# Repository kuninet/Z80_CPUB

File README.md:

# Z80マイコンCPUボード (KZ80-CPUB)

- SBC8080バスにつながるZ80 CPUボード KZ80-CPUB のデータ類です。
  - CPUボード+[SBC8080 SUBルーズキット](https://vintagechips.wordpress.com/2018/06/23/sbc8080-subルーズキット/)などとのセットでコンピューターとして動作します。(単独では動きません)

- 回路図、部品等の詳しい説明を記載したwikiページは以下になります。
  - https://github.com/kuninet/Z80_CPUB/wiki

## ファイル/ディレクトリ

ファイル/ディレクトリの構成は以下のとおりです

|ファイル/ディレクトリ|概要|
|:--|:--|
|KiCAD/PCB/|基板製造用ガーバーファイル等|
|KiCAD/Z80-CPUB.ods|部品一覧表|
|img/Z80-CPUB.pdf|回路図 PDF版|
|KiCAD/Z80-CPUB*.*|KiCADファイル|

## 注意点

- REV1基板はSBC8080ルーズキットと完全互換ではありません。
  - DMAは行なえません。(#BUSREQ/#BUSACKに対応していない)
  - DMAに伴う#IOR/Wや#MEMR/Wのハイインピーダンス対応を実施していません。

## ライセンス

- 本リポジトリのデータは MIT License のもとで公開します。[LICENSE.txt](LICENSE.txt)を参照して下さい。

## 参照

[電脳伝説:SBC8080ルーズキット](https://vintagechips.wordpress.com/2018/06/24/sbc8080-cpu%E3%83%AB%E3%83%BC%E3%82%BA%E3%82%AD%E3%83%83%E3%83%88/)

[SBC8080 SUBボードへつなぐZ80 CPUボードの作成](https://kuninet.org/2018/08/01/sbc8080-subボードへつなぐz80-cpuボードの作成/)

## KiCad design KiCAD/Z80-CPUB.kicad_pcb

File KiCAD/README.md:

# Z80 CPUボード

## 概要

- SBC8080ルーズキットのバス(SBC8080バスと呼称)につながるZ80 CPUボードのKiCADデータです。

## ファイル/ディレクトリ

ファイル/ディレクトリの構成は以下のとおりです

|ファイル/ディレクトリ|概要|
|:--|:--|
|PCB/|基板製造用ガーバーファイル等|
|Z80-CPUB.ods|部品一覧表|
|Z80-CPUB.pdf|回路図 PDF版|
|Z80-CPUB*.*|KiCADファイル|

## 注意点

- REV1基板は、SBC8080ルーズキットと完全互換ではありません。
  - DMAは行なえません。(#BUSREQ/#BUSACKに対応していない)
  - DMAに伴う#IOR/Wや#MEMR/Wのハイインピーダンス対応を実施していません。

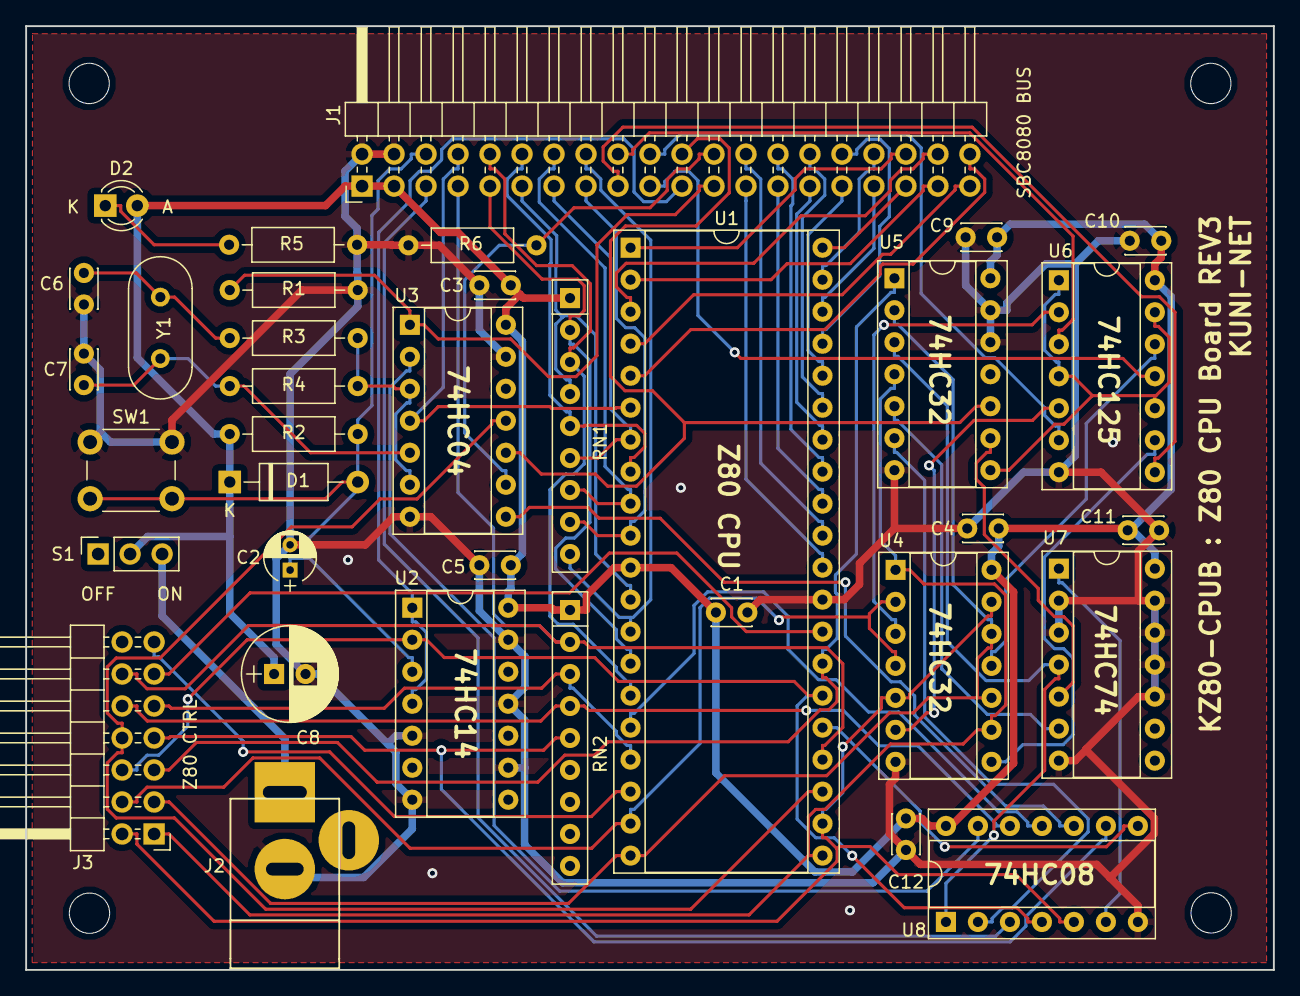
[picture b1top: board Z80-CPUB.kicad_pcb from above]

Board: 2 copper layers, 99.1 x 74.9 mm, 40 parts (0 on the bottom side), 69 nets.

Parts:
C1, C3, C4, C5, C9, C10, C11, C12: 0.1u; C_Disc_D3.0mm_W2.0mm_P2.50mm
C2: 47u; CP_Radial_D4.0mm_P2.00mm
C6, C7: 22p; C_Disc_D3.0mm_W2.0mm_P2.50mm
C8: 100u; CP_Radial_D7.5mm_P2.50mm
D1: D; D_A-405_P10.16mm_Horizontal
D2: LED; LED_D3.0mm
J1: SBC8080 BUS; PinHeader_2x20_P2.54mm_Horizontal
J2: Jack-DC; JACK_ALIM
J3: Z80 CTL; PinHeader_2x07_P2.54mm_Horizontal
M1, M2, M3, M4: MountingHole_3M; MountingHole_3.2mm_M3
R1, R2, R6: 4.7k; R_Axial_DIN0207_L6.3mm_D2.5mm_P10.16mm_Horizontal
R3, R5: 1k; R_Axial_DIN0207_L6.3mm_D2.5mm_P10.16mm_Horizontal
R4: 1M; R_Axial_DIN0207_L6.3mm_D2.5mm_P10.16mm_Horizontal
RN1: 10k; R_Array_SIP9
RN2: 4.7k; R_Array_SIP9
S1: SW; PinSocket_1x03_P2.54mm_Vertical
SW1: RESET SW; SW_PUSH_6mm_H4.3mm
U1: Z80CPU; DIP-40_W15.24mm_Socket
U2: 74HC14; DIP-14_W7.62mm_Socket
U3: 74HC04; DIP-14_W7.62mm_Socket
U4, U5: 74HC32; DIP-14_W7.62mm_Socket
U6: 74HC125; DIP-14_W7.62mm_Socket
U7: 74HC74; DIP-14_W7.62mm_Socket
U8: 74HC08; DIP-14_W7.62mm_Socket
Y1: 7.3728MHz; Crystal_HC49-U_Vertical

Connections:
A0: J1.25, U1.30
A1: J1.26, U1.31
A2: J1.27, U1.32
A3: J1.28, U1.33
A4: J1.29, U1.34
A5: J1.30, U1.35
A6: J1.31, U1.36
A7: J1.32, U1.37
A8: J1.33, U1.38
A9: J1.34, U1.39
A10: J1.35, U1.40
A11: J1.36, U1.1
A12: J1.37, U1.2
A13: J1.38, U1.3
A14: J1.39, U1.4
A15: J1.40, U1.5
CLK: J1.8, U1.6, U3.4
D0: J1.9, RN1.2, U1.14
D1: J1.10, RN1.3, U1.15
D2: J1.11, RN1.4, U1.12
D3: J1.12, RN1.5, U1.8
D4: J1.13, RN1.6, U1.7
D5: J1.14, RN1.7, U1.9
D6: J1.15, RN1.8, U1.10
D7: J1.16, RN1.9, U1.13
GND: C1.2, C2.2, C3.2, C4.2, C5.2, C6.2, C7.2, C8.2, C9.2, C10.2, C11.2, C12.2, J1.2, J1.4, J2.2, R1.2, R5.2, R6.2, SW1.1, U1.29, U2.5, U2.7, U2.9, U2.11, U2.13, U3.7, U3.13, U4.7, U5.7, U5.12, U5.13, U6.7, U7.2, U7.3, U7.7, U7.10, U7.11, U7.12, U7.13, U8.7
HLDA: J1.22, U3.10, U5.10
HOLD: J1.24, R6.1, U3.9
INT: J1.23, R1.1, U3.1
unnamed: C6.1, R3.2, Y1.1
unnamed: C7.1, R4.2, U3.5, Y1.2
unnamed: D2.1, R5.1
unnamed: J2.1, S1.3
unnamed: R3.1, R4.1, U3.3, U3.6
unnamed: U3.2, U8.13
unnamed: U3.8, U8.10
unnamed: U4.3, U6.2
unnamed: U4.6, U6.5
unnamed: U4.8, U6.9
unnamed: U4.11, U6.12
unnamed: U5.3, U7.4, U8.1
unnamed: U5.5, U7.6
unnamed: U5.6, U8.2
unnamed: U5.8, U6.1, U6.4, U6.10, U6.13
unnamed: U5.9, U7.5
unnamed: U7.1, U8.6
RDYIN: J1.7, J3.12, RN2.2, U1.24
RES: J1.21, U2.1, U2.4
RN22: J3.9, RN2.3, U1.17
RN23: J3.10, RN2.4, U8.12
RN24: J3.7, RN2.5, U8.9
VCC: C1.1, C3.1, C4.1, C5.1, C8.1, C9.1, C10.1, C11.1, C12.1, D1.1, D2.2, J1.1, J1.3, R2.1, RN1.1, RN2.1, S1.2, U1.11, U2.14, U3.14, U4.14, U5.14, U6.14, U7.14, U8.14
~BUSACK: J3.8, U1.23, U3.11
~BUSREQ: U1.25, U8.8
~HALT: J3.13, U1.18
~INT: U1.16, U8.11
~INTA: J1.5, U8.3
~IORD: J1.17, U6.8
~IOREQ: J3.3, U1.20, U4.10, U4.12, U5.2
~IOWR: J1.19, U6.11
~M1: J3.5, U1.27, U5.1
~MEMRD: J1.18, U6.3
~MEMWR: J1.20, U6.6
~MREQ: J3.4, U1.19, U4.2, U4.4
~RD: J3.1, U1.21, U4.1, U4.9, U5.4
~RESET: J3.6, U1.26, U2.2, U8.4
~RESIN: C2.1, D1.2, J1.6, R2.2, SW1.2, U2.3
~RFSH: J3.11, U1.28
~WR: J3.2, U1.22, U4.5, U4.13, U8.5

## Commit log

2018-09-13 init commit
2018-09-13 ディレクトリIOB/とRAMB/追加
2018-09-13 CPUボードREADME修正
2018-09-13 メモリーボードREADME追加
2018-09-30 ディレクトリレイアウト変更
2018-10-07 ボード命名&シルク修正
2018-10-08 r1.1 最終確認
2018-10-08 水晶発信のため74HC04はCMOS必須と明記
2018-10-17 PDF差し替え
2018-10-28 部品リストで、74HC04の代替品を修正
2018-12-17 R5 抵抗値変更
2019-03-17 REV2 回路図、製造データ出力
2019-03-17 旧回路図(REV1) 別ファイルへ
2019-03-23 REV2.1検討開始 回路図、パターン変更
2019-09-07 REV3基板パターン、ガーバーデータ出力
2019-09-07 回路図 REV3版出力
2019-09-08 シルク見直し、ガーバーデータ出力
2019-09-11 背面シルク追加、ガーバーデータ再出力
